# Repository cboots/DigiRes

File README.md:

DigiRes
=======

Arduino based digitally controlled resistor array. Contains all the code and hardware designs needed to recreate the project.

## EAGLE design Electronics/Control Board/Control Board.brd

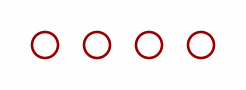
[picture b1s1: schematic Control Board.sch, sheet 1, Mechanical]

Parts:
STANDOFF1, STANDOFF2, STANDOFF3, STANDOFF4: STAND-OFF

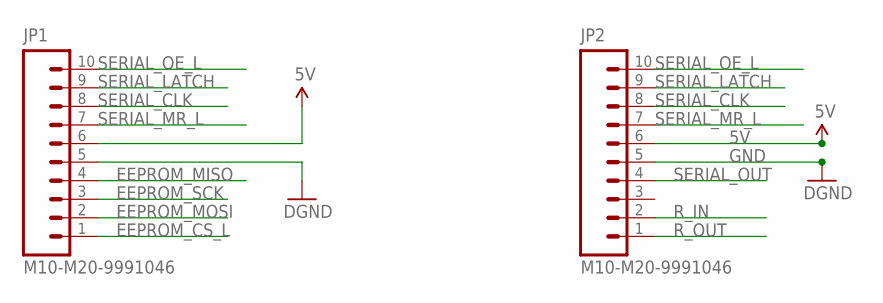
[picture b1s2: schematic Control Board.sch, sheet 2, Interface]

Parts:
JP1, JP2: M10-M20-9991046; M20-9991046

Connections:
5V: JP1.6, JP2.6; also elsewhere on the board
EEPROM_CS_L: JP1.1
EEPROM_MISO: JP1.4
EEPROM_MOSI: JP1.2
EEPROM_SCK: JP1.3
GND: JP1.5, JP2.5; also elsewhere on the board
R_IN: JP2.2
R_OUT: JP2.1
SERIAL_CLK: JP1.8, JP2.8
SERIAL_LATCH: JP1.9, JP2.9
SERIAL_MR_L: JP1.7, JP2.7
SERIAL_OE_L: JP1.10, JP2.10
SERIAL_OUT: JP2.4

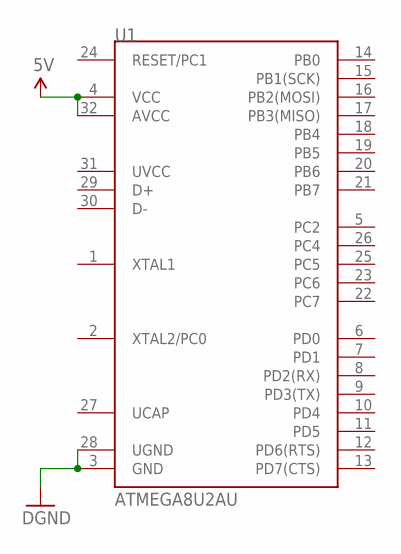
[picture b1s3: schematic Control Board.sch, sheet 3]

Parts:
U1: ATMEGA8U2AU; TQFP32-08

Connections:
5V: U1.4 (VCC), U1.32 (AVCC); also elsewhere on the board
GND: U1.3 (GND), U1.28 (UGND); also elsewhere on the board

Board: 2 copper layers, 7 parts (2 on the bottom side), 6 nets, no tracks yet.

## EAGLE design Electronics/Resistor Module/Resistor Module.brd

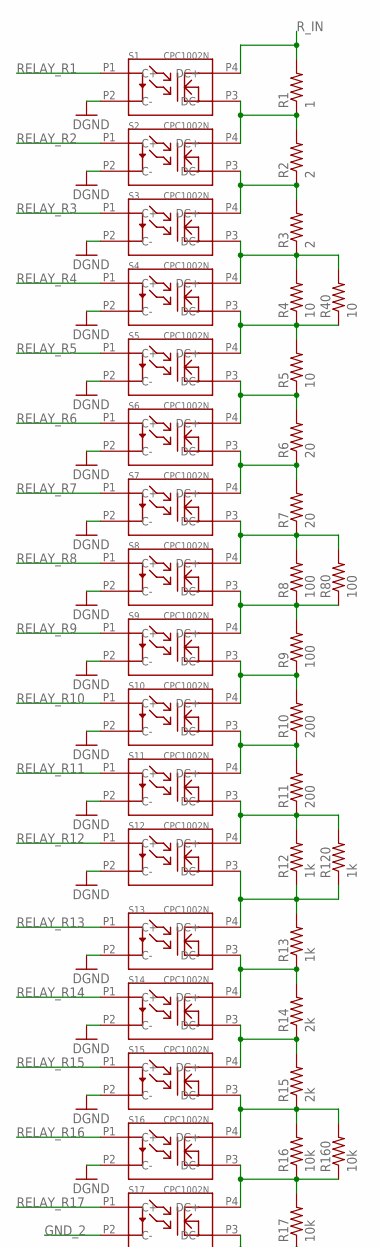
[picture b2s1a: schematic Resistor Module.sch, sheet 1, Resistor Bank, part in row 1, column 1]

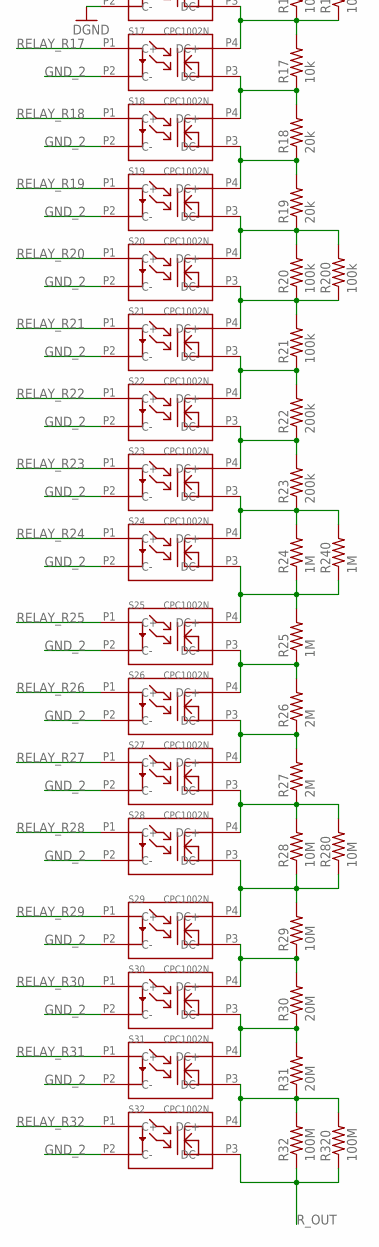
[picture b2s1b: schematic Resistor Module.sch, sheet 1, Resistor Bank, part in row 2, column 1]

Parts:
R1: 1; 1206
R2, R3: 2; 1206
R4, R5, R40: 10; 1206
R6, R7: 20; 1206
R8, R9, R80: 100; 1206
R10, R11: 200; 1206
R12, R13, R120: 1k; 1206
R14, R15: 2k; 1206
R16, R17, R160: 10k; 1206
R18, R19: 20k; 1206
R20, R21, R200: 100k; 1206
R22, R23: 200k; 1206
R24, R25, R240: 1M; 1206
R26, R27: 2M; 1206
R28, R29, R280: 10M; 1206
R30, R31: 20M; 1206
R32, R320: 100M; 1206
S1, S2, S3, S4, S5, S6, S7, S8, S9, S10, S11, S12, S13, S14, S15, S16, S17, S18, S19, S20, S21, S22, S23, S24, S25, S26, S27, S28, S29, S30, S31, S32: CPC1002N

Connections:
GND: S1.P2 (C-), S2.P2 (C-), S3.P2 (C-), S4.P2 (C-), S5.P2 (C-), S6.P2 (C-), S7.P2 (C-), S8.P2 (C-), S9.P2 (C-), S10.P2 (C-), S11.P2 (C-), S12.P2 (C-), S13.P2 (C-), S14.P2 (C-), S15.P2 (C-), S16.P2 (C-); also elsewhere on the board
GND_2: S17.P2 (C-), S18.P2 (C-), S19.P2 (C-), S20.P2 (C-), S21.P2 (C-), S22.P2 (C-), S23.P2 (C-), S24.P2 (C-), S25.P2 (C-), S26.P2 (C-), S27.P2 (C-), S28.P2 (C-), S29.P2 (C-), S30.P2 (C-), S31.P2 (C-), S32.P2 (C-); also elsewhere on the board
unnamed: R2.1, R3.2, S2.P3 (DC-), S3.P4 (DC+)
unnamed: R3.1, R4.2, R40.2, S3.P3 (DC-), S4.P4 (DC+)
unnamed: R4.1, R5.2, R40.1, S4.P3 (DC-), S5.P4 (DC+)
unnamed: R5.1, R6.2, S5.P3 (DC-), S6.P4 (DC+)
unnamed: R6.1, R7.2, S6.P3 (DC-), S7.P4 (DC+)
unnamed: R7.1, R8.2, R80.2, S7.P3 (DC-), S8.P4 (DC+)
unnamed: R9.1, R10.2, S9.P3 (DC-), S10.P4 (DC+)
unnamed: R10.1, R11.2, S10.P3 (DC-), S11.P4 (DC+)
unnamed: R11.1, R12.2, R120.2, S11.P3 (DC-), S12.P4 (DC+)
unnamed: R1.1, R2.2, S1.P3 (DC-), S2.P4 (DC+)
unnamed: R14.1, R15.2, S14.P3 (DC-), S15.P4 (DC+)
unnamed: R15.1, R16.2, R160.2, S15.P3 (DC-), S16.P4 (DC+)
unnamed: R17.1, R18.2, S17.P3 (DC-), S18.P4 (DC+)
unnamed: R18.1, R19.2, S18.P3 (DC-), S19.P4 (DC+)
unnamed: R19.1, R20.2, R200.2, S19.P3 (DC-), S20.P4 (DC+)
unnamed: R20.1, R21.2, R200.1, S20.P3 (DC-), S21.P4 (DC+)
unnamed: R21.1, R22.2, S21.P3 (DC-), S22.P4 (DC+)
unnamed: R22.1, R23.2, S22.P3 (DC-), S23.P4 (DC+)
unnamed: R23.1, R24.2, R240.2, S23.P3 (DC-), S24.P4 (DC+)
unnamed: R13.1, R14.2, S13.P3 (DC-), S14.P4 (DC+)
unnamed: R24.1, R25.2, R240.1, S24.P3 (DC-), S25.P4 (DC+)
unnamed: R28.1, R29.2, R280.1, S28.P3 (DC-), S29.P4 (DC+)
unnamed: R25.1, R26.2, S25.P3 (DC-), S26.P4 (DC+)
unnamed: R26.1, R27.2, S26.P3 (DC-), S27.P4 (DC+)
unnamed: R27.1, R28.2, R280.2, S27.P3 (DC-), S28.P4 (DC+)
unnamed: R29.1, R30.2, S29.P3 (DC-), S30.P4 (DC+)
unnamed: R30.1, R31.2, S30.P3 (DC-), S31.P4 (DC+)
unnamed: R31.1, R32.2, R320.2, S31.P3 (DC-), S32.P4 (DC+)
R80: R8.1, R9.2, R80.1, S8.P3 (DC-), S9.P4 (DC+)
R120: R12.1, R13.2, R120.1, S12.P3 (DC-), S13.P4 (DC+)
R160: R16.1, R17.2, R160.1, S16.P3 (DC-), S17.P4 (DC+)
RELAY_R1: S1.P1 (C+); also elsewhere on the board
RELAY_R2: S2.P1 (C+); also elsewhere on the board
RELAY_R3: S3.P1 (C+); also elsewhere on the board
RELAY_R4: S4.P1 (C+); also elsewhere on the board
RELAY_R5: S5.P1 (C+); also elsewhere on the board
RELAY_R6: S6.P1 (C+); also elsewhere on the board
RELAY_R7: S7.P1 (C+); also elsewhere on the board
RELAY_R8: S8.P1 (C+); also elsewhere on the board
RELAY_R9: S9.P1 (C+); also elsewhere on the board
RELAY_R10: S10.P1 (C+); also elsewhere on the board
RELAY_R11: S11.P1 (C+); also elsewhere on the board
RELAY_R12: S12.P1 (C+); also elsewhere on the board
RELAY_R13: S13.P1 (C+); also elsewhere on the board
RELAY_R14: S14.P1 (C+); also elsewhere on the board
RELAY_R15: S15.P1 (C+); also elsewhere on the board
RELAY_R16: S16.P1 (C+); also elsewhere on the board
RELAY_R17: S17.P1 (C+); also elsewhere on the board
RELAY_R18: S18.P1 (C+); also elsewhere on the board
RELAY_R19: S19.P1 (C+); also elsewhere on the board
RELAY_R20: S20.P1 (C+); also elsewhere on the board
RELAY_R21: S21.P1 (C+); also elsewhere on the board
RELAY_R22: S22.P1 (C+); also elsewhere on the board
RELAY_R23: S23.P1 (C+); also elsewhere on the board
RELAY_R24: S24.P1 (C+); also elsewhere on the board
RELAY_R25: S25.P1 (C+); also elsewhere on the board
RELAY_R26: S26.P1 (C+); also elsewhere on the board
RELAY_R27: S27.P1 (C+); also elsewhere on the board
RELAY_R28: S28.P1 (C+); also elsewhere on the board
RELAY_R29: S29.P1 (C+); also elsewhere on the board
RELAY_R30: S30.P1 (C+); also elsewhere on the board
RELAY_R31: S31.P1 (C+); also elsewhere on the board
RELAY_R32: S32.P1 (C+); also elsewhere on the board
R_IN: R1.2, S1.P4 (DC+); also elsewhere on the board
R_OUT: R32.1, R320.1, S32.P3 (DC-); also elsewhere on the board

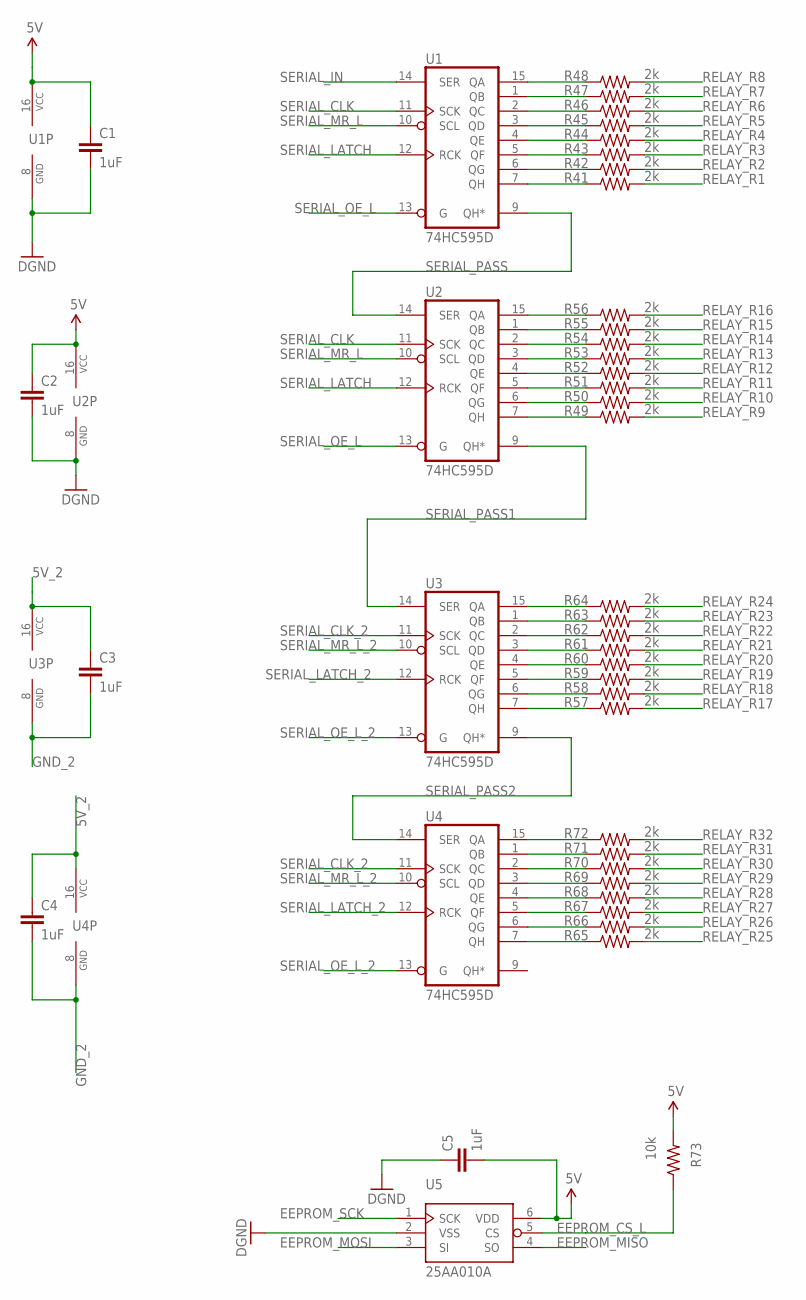
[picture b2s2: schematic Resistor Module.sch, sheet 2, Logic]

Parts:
C1, C2, C3, C4, C5: 1uF; 0603-CAP
R41, R42, R43, R44, R45, R46, R47, R48, R49, R50, R51, R52, R53, R54, R55, R56, R57, R58, R59, R60, R61, R62, R63, R64, R65, R66, R67, R68, R69, R70, R71, R72: 2k; 0603-RES
R73: 10k; 0603-RES
U1, U2, U3, U4: 74HC595D; SO16
U5: 25AA010A; SOT23-6

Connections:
5V: C1.1, C2.1, C5.2, R73.2, U1.16 (VCC), U2.16 (VCC), U5.6 (VDD); also elsewhere on the board
5V_2: C3.1, C4.1, U3.16 (VCC), U4.16 (VCC); also elsewhere on the board
EEPROM_CS_L: R73.1, U5.5 (CS); also elsewhere on the board
EEPROM_MISO: U5.4 (SO); also elsewhere on the board
EEPROM_MOSI: U5.3 (SI); also elsewhere on the board
EEPROM_SCK: U5.1 (SCK); also elsewhere on the board
GND: C1.2, C2.2, C5.1, U1.8 (GND), U2.8 (GND), U5.2 (VSS); also elsewhere on the board
GND_2: C3.2, C4.2, U3.8 (GND), U4.8 (GND); also elsewhere on the board
unnamed: R48.1, U1.15 (QA)
unnamed: R47.1, U1.1 (QB)
unnamed: R46.1, U1.2 (QC)
unnamed: R45.1, U1.3 (QD)
unnamed: R44.1, U1.4 (QE)
unnamed: R43.1, U1.5 (QF)
unnamed: R42.1, U1.6 (QG)
unnamed: R41.1, U1.7 (QH)
unnamed: R56.1, U2.15 (QA)
unnamed: R55.1, U2.1 (QB)
unnamed: R54.1, U2.2 (QC)
unnamed: R53.1, U2.3 (QD)
unnamed: R52.1, U2.4 (QE)
unnamed: R51.1, U2.5 (QF)
unnamed: R50.1, U2.6 (QG)
unnamed: R49.1, U2.7 (QH)
unnamed: R64.1, U3.15 (QA)
unnamed: R63.1, U3.1 (QB)
unnamed: R62.1, U3.2 (QC)
unnamed: R61.1, U3.3 (QD)
unnamed: R60.1, U3.4 (QE)
unnamed: R59.1, U3.5 (QF)
unnamed: R58.1, U3.6 (QG)
unnamed: R57.1, U3.7 (QH)
unnamed: R72.1, U4.15 (QA)
unnamed: R71.1, U4.1 (QB)
unnamed: R70.1, U4.2 (QC)
unnamed: R69.1, U4.3 (QD)
unnamed: R68.1, U4.4 (QE)
unnamed: R67.1, U4.5 (QF)
unnamed: R66.1, U4.6 (QG)
unnamed: R65.1, U4.7 (QH)
RELAY_R1: R41.2; also elsewhere on the board
RELAY_R2: R42.2; also elsewhere on the board
RELAY_R3: R43.2; also elsewhere on the board
RELAY_R4: R44.2; also elsewhere on the board
RELAY_R5: R45.2; also elsewhere on the board
RELAY_R6: R46.2; also elsewhere on the board
RELAY_R7: R47.2; also elsewhere on the board
RELAY_R8: R48.2; also elsewhere on the board
RELAY_R9: R49.2; also elsewhere on the board
RELAY_R10: R50.2; also elsewhere on the board
RELAY_R11: R51.2; also elsewhere on the board
RELAY_R12: R52.2; also elsewhere on the board
RELAY_R13: R53.2; also elsewhere on the board
RELAY_R14: R54.2; also elsewhere on the board
RELAY_R15: R55.2; also elsewhere on the board
RELAY_R16: R56.2; also elsewhere on the board
RELAY_R17: R57.2; also elsewhere on the board
RELAY_R18: R58.2; also elsewhere on the board
RELAY_R19: R59.2; also elsewhere on the board
RELAY_R20: R60.2; also elsewhere on the board
RELAY_R21: R61.2; also elsewhere on the board
RELAY_R22: R62.2; also elsewhere on the board
RELAY_R23: R63.2; also elsewhere on the board
RELAY_R24: R64.2; also elsewhere on the board
RELAY_R25: R65.2; also elsewhere on the board
RELAY_R26: R66.2; also elsewhere on the board
RELAY_R27: R67.2; also elsewhere on the board
RELAY_R28: R68.2; also elsewhere on the board
RELAY_R29: R69.2; also elsewhere on the board
RELAY_R30: R70.2; also elsewhere on the board
RELAY_R31: R71.2; also elsewhere on the board
RELAY_R32: R72.2; also elsewhere on the board
SERIAL_CLK: U1.11 (SCK), U2.11 (SCK); also elsewhere on the board
SERIAL_CLK_2: U3.11 (SCK), U4.11 (SCK); also elsewhere on the board
SERIAL_IN: U1.14 (SER); also elsewhere on the board
SERIAL_LATCH: U1.12 (RCK), U2.12 (RCK); also elsewhere on the board
SERIAL_LATCH_2: U3.12 (RCK), U4.12 (RCK); also elsewhere on the board
SERIAL_MR_L: U1.10 (SCL), U2.10 (SCL); also elsewhere on the board
SERIAL_MR_L_2: U3.10 (SCL), U4.10 (SCL); also elsewhere on the board
SERIAL_OE_L: U1.13 (G), U2.13 (G); also elsewhere on the board
SERIAL_OE_L_2: U3.13 (G), U4.13 (G); also elsewhere on the board
SERIAL_PASS: U1.9 (QH*), U2.14 (SER)
SERIAL_PASS1: U2.9 (QH*), U3.14 (SER)
SERIAL_PASS2: U3.9 (QH*), U4.14 (SER)

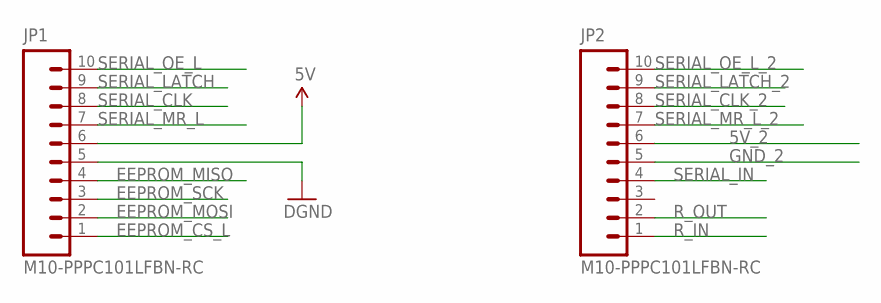
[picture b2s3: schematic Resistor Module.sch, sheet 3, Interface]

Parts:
JP1, JP2: M10-PPPC101LFBN-RC; PPPC101LFBN-RC

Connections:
5V: JP1.6; also elsewhere on the board
5V_2: JP2.6; also elsewhere on the board
EEPROM_CS_L: JP1.1; also elsewhere on the board
EEPROM_MISO: JP1.4; also elsewhere on the board
EEPROM_MOSI: JP1.2; also elsewhere on the board
EEPROM_SCK: JP1.3; also elsewhere on the board
GND: JP1.5; also elsewhere on the board
GND_2: JP2.5; also elsewhere on the board
R_IN: JP2.1; also elsewhere on the board
R_OUT: JP2.2; also elsewhere on the board
SERIAL_CLK: JP1.8; also elsewhere on the board
SERIAL_CLK_2: JP2.8; also elsewhere on the board
SERIAL_IN: JP2.4; also elsewhere on the board
SERIAL_LATCH: JP1.9; also elsewhere on the board
SERIAL_LATCH_2: JP2.9; also elsewhere on the board
SERIAL_MR_L: JP1.7; also elsewhere on the board
SERIAL_MR_L_2: JP2.7; also elsewhere on the board
SERIAL_OE_L: JP1.10; also elsewhere on the board
SERIAL_OE_L_2: JP2.10; also elsewhere on the board

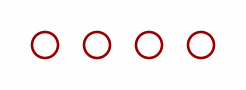
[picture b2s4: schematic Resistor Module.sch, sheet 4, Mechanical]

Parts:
STANDOFF1, STANDOFF2, STANDOFF3, STANDOFF4: STAND-OFF

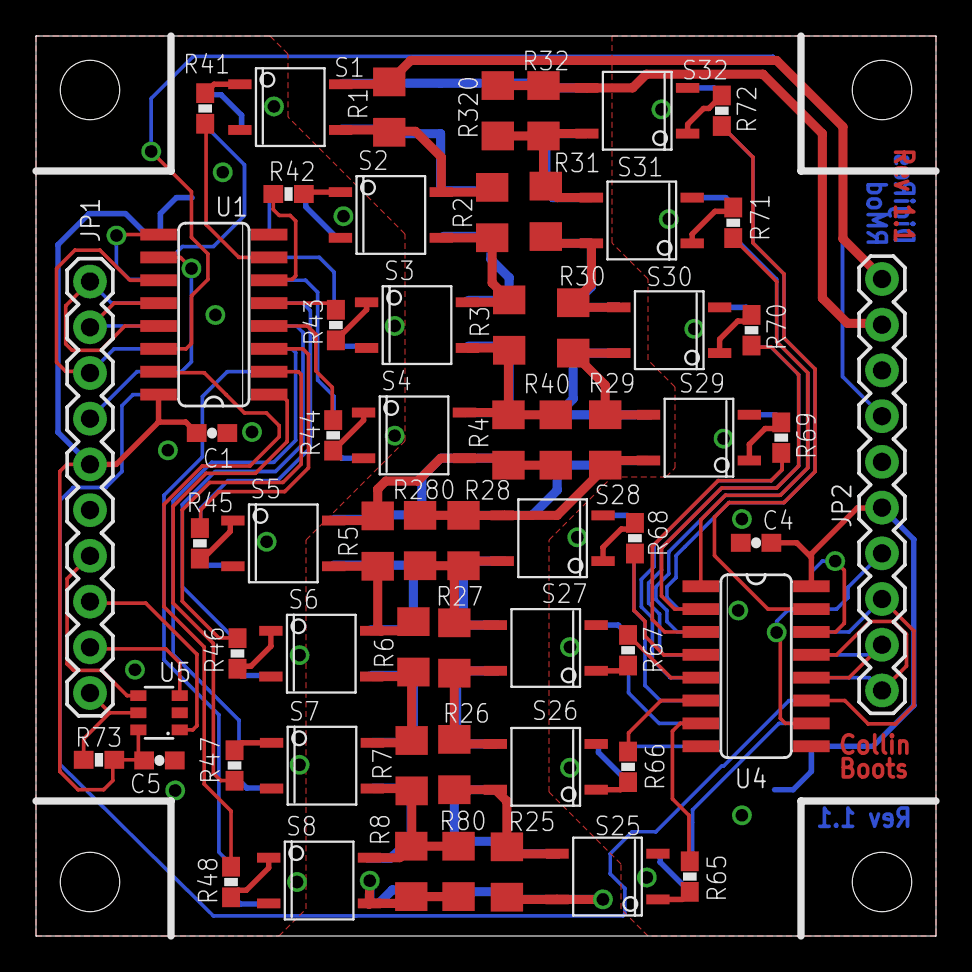
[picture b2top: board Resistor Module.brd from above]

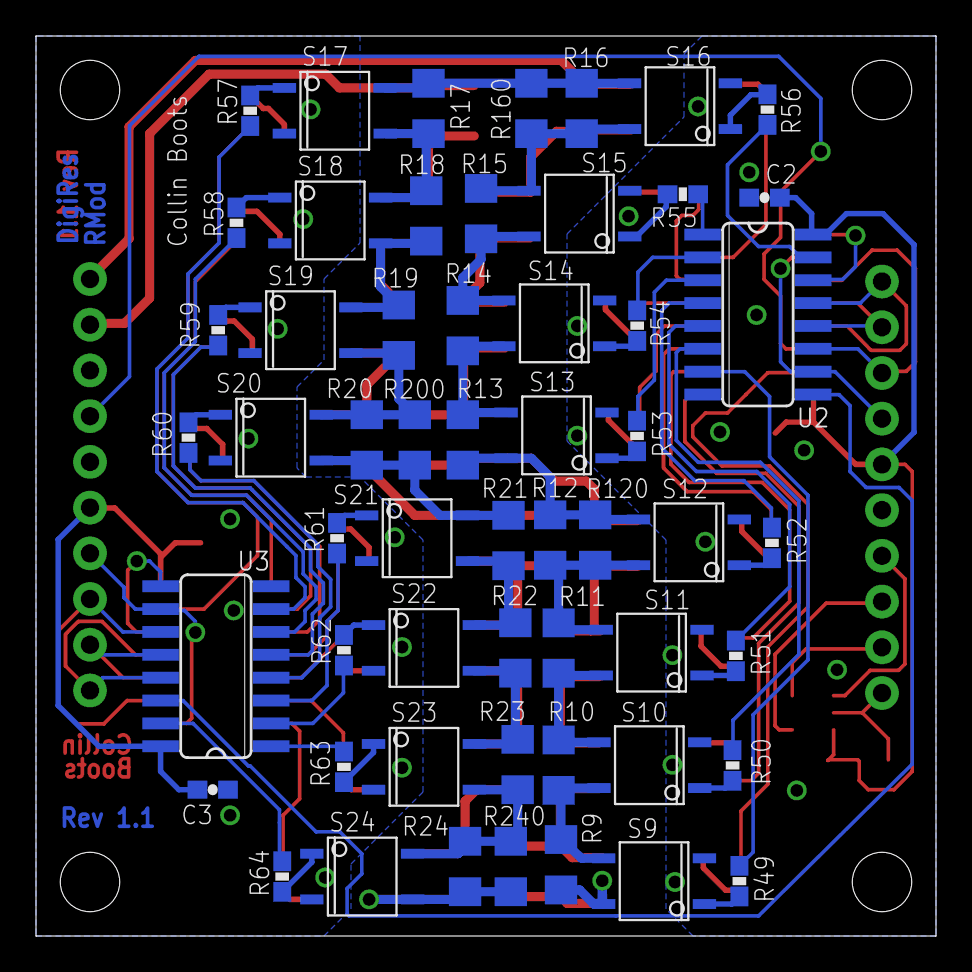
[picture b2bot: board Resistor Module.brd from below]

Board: 2 copper layers, 50.0 x 50.0 mm, 121 parts (56 on the bottom side), 117 nets.

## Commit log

2013-08-19 Initial commit of design.
    Needs review, layout, and routing, but resistor module should be near completion.
    Added sketchup model used to sketch out enclosure design and board to board interfaces
2013-08-21 Finished layout of resistor module
2013-08-22 Finished layout and updated sketch. Discovered I could fit entire range on a single node if I double back the thing, so gonna do that instead. Who needs modularity when the entire thing fits on one b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
2013-08-29 Reworking resistor module to fit everything on a single module
2013-08-29 Added Control Board Library.lbr
2013-08-29 Updated readme as a test.
2013-08-30 Updated schematic for full range module. 1/4 layout done.
2013-08-30 Placed another 1/4 of the board. Top layer preliminary completed
2013-08-30 Placed all relays and critical resistors.
2013-08-30 Everything in it's place
2013-08-30 Updated body sketch with new layout
2013-08-31 Routed main resistance path on both sides. Need to redo order on serial ports
2013-08-31 Tied control nets for serial shifters to connectors and each other. Only need to route relay signals now.
2013-08-31 Finished routing. Was more convenient for routing to use inverted byte order for the serial passing.
2013-08-31 Finished routing and silk cleanup. Ready for final review and release.
2013-08-31 Added project outputs for initial DFM run. Need to add slik labels, descriptions, and iconography before ordering.
2013-08-31 Added silk documentation and part numbers. Fixed a few minor placement issues and silk errors. Updated gerbers for manufacture and completed review. Will submit for DFM and order boards today hopeful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
2013-09-01 Added filler for control module and flushed out body sketch some more. Added two more displays
2013-09-01 Added Binding posts to resistor box. Looks kinda silly
2013-09-01 Added battery and no battery variations to package
2013-09-07 Started work on control board.
2013-09-09 Added atmega chips to library
2013-09-11 Selected 8U2 microchip for main controller. Don't need a lot of IO and needed included USB drive
